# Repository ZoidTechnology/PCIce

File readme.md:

# PCIce
A PCI Express card with an inbuilt PWM fan controller and mounting points for an 80mm fan.

PCIce is available to buy on [Tindie](https://www.tindie.com/products/code7/pcice/).  
More information can be found on my [website](https://zoid.com.au/pcice/).
## Hardware
The hardware is based on an ATtiny13A which outputs a 25kHz PWM signal to the fan. A button is used for speed control, and the current speed is displayed on four multiplexed LEDs.
## Firmware
### Functionality
The firmware attempts to load the speed setting from EEPROM on boot. The speed setting is stored twice to guard against corruption. The second copy is inverted to detect a blank EEPROM. The speed will default to maximum if corruption is detected to prevent overheating. The button is debounced in software and must be released for a short period before the next press is registered.
### Building
The firmware can be compiled and flashed with the `build` script inside the firmware directory. This script expects an AVRISP MKII to be connected over USB. `avr-gcc`, `avr-objcopy`, `avrdude` and `avr-libc` are required to build the firmware.
## License
PCIce is licensed under the GNU GPLv3 license. This license does not cover the use of Zoid Technology trademarks. A list of trademarks can be found [here](https://zoid.com.au/trademarks/).

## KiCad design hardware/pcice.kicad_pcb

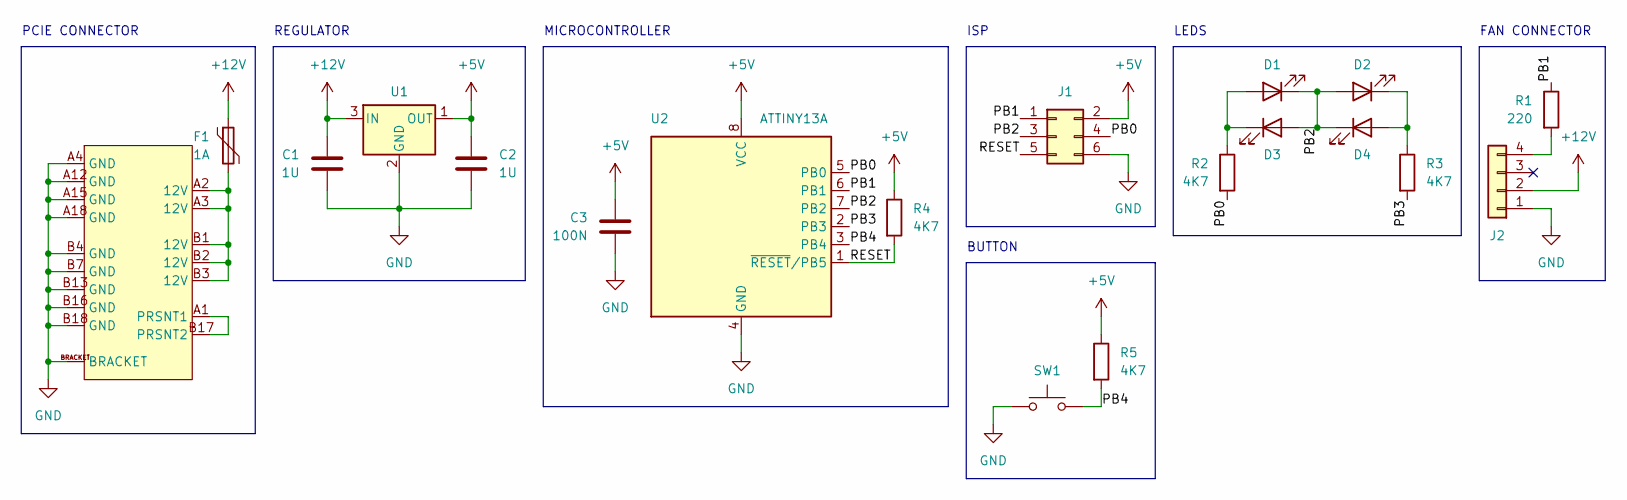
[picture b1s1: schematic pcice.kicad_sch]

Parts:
C1, C2: 1U; C_0805
C3: 100N; C_0805
D1, D2, D3, D4: LED; LED_0805
F1: 1A; F_1812
J1: CON 2X3; GENERIC_IDC_2X3
J2: CON 3+1; 744-81-04TB1B
J3: PCIE X1 12V; PCIE_X1_12V
R1: 220; R_0805
R2, R3, R4, R5: 4K7; R_0805
SW1: LPTS; GENERIC_LOW_PROFILE_SWITCH
U1: 5V SOT-89 REG; SOT89-3
U2: ATTINY13A; SOIC-8

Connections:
+5V: C2.1, C3.1, J1.2, R4.1, R5.1, U1.1 (OUT), U2.8 (VCC)
+12V: C1.1, F1.1, J2.2, U1.3 (IN)
/PB0: J1.4, R2.2, U2.5 (PB0)
/PB1: J1.1, R1.1, U2.6 (PB1)
/PB2: D1.1 (K), D2.2 (A), D3.2 (A), D4.1 (K), J1.3, U2.7 (PB2)
/PB3: R3.2, U2.2 (PB3)
/PB4: R5.2, SW1.2, U2.3 (PB4)
/RESET: J1.5, R4.2, U2.1 (~RESET/PB5)
GND: C1.2, C2.2, C3.2, J1.6, J2.1, J3.A4 (GND), J3.A12 (GND), J3.A15 (GND), J3.A18 (GND), J3.B4 (GND), J3.B7 (GND), J3.B13 (GND), J3.B16 (GND), J3.B18 (GND), J3.BRACKET, SW1.1, U1.2 (GND), U2.4 (GND)
unnamed: D1.2 (A), D3.1 (K), R2.1
unnamed: D2.1 (K), D4.2 (A), R3.1
unnamed: F1.2, J3.A2 (12V), J3.A3 (12V), J3.B1 (12V), J3.B2 (12V), J3.B3 (12V)
unnamed: J2.4, R1.2
unnamed: J3.A1 (PRSNT1), J3.B17 (PRSNT2)

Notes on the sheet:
REGULATOR
MICROCONTROLLER
FAN CONNECTOR
PCIE CONNECTOR
LEDS
ISP
BUTTON

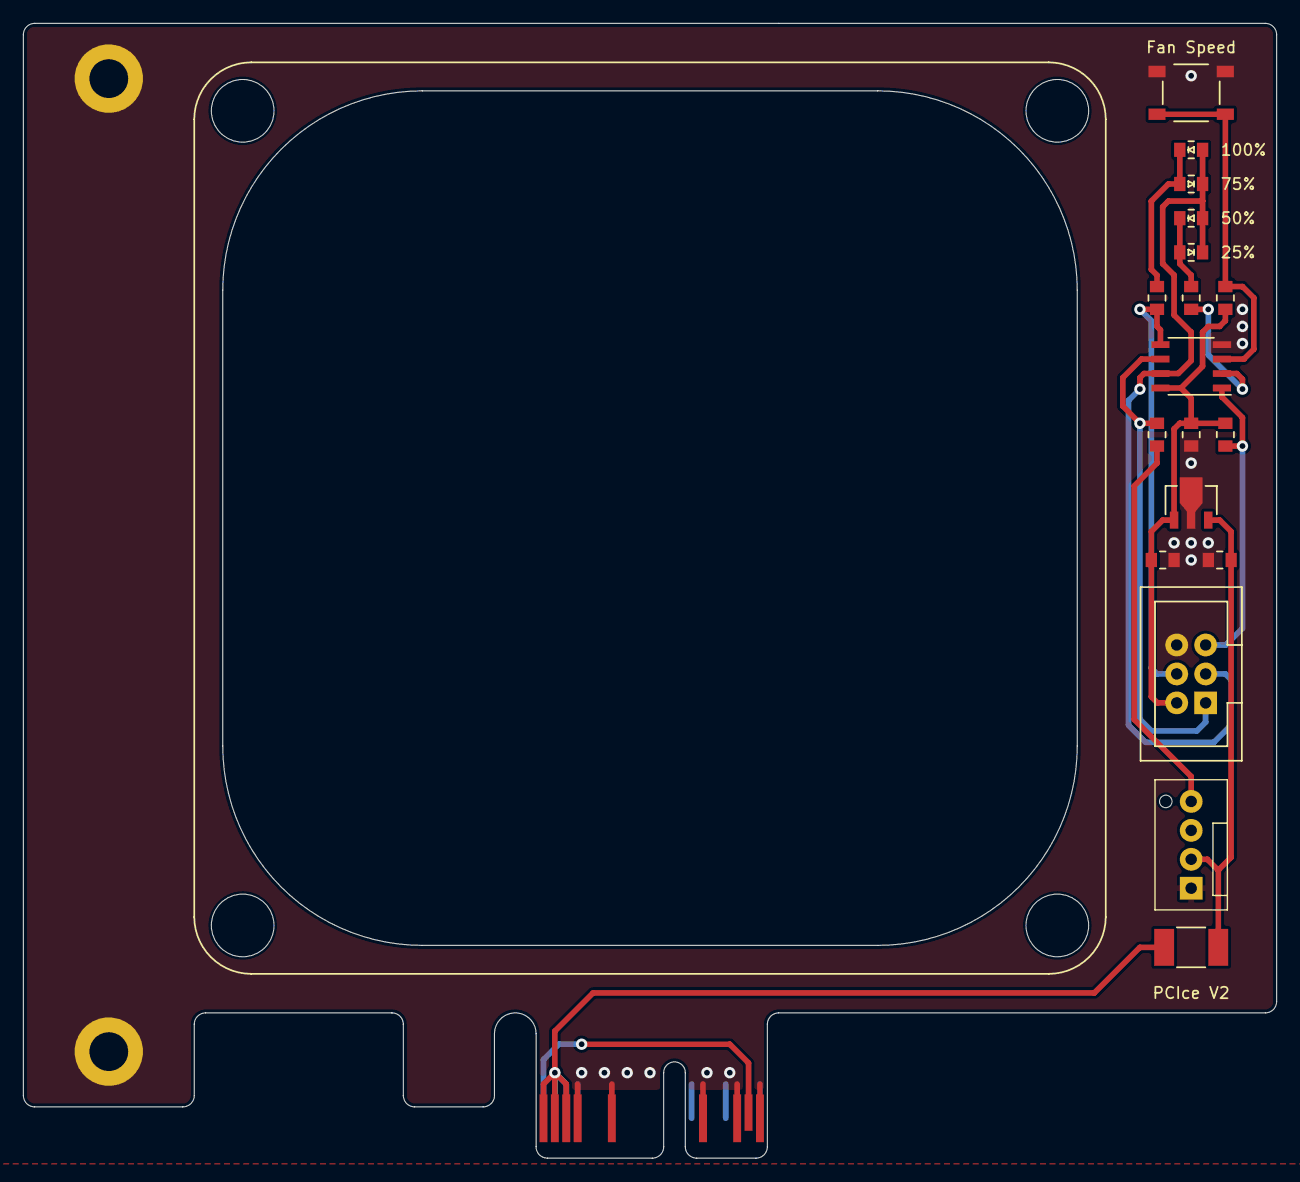
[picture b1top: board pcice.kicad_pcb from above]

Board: 2 copper layers, 110.0 x 99.6 mm, 19 parts (0 on the bottom side), 14 nets.

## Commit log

2022-12-26 Added readme
2022-12-26 Fixed spelling mistake
2023-03-03 Enable BOD to prevent unintended behaviour at low voltages
2023-03-04 Added Tindie and website link to readme
2023-04-03 Added hardware files
2023-04-22 Added license information
2024-07-22 Update Tindie link
